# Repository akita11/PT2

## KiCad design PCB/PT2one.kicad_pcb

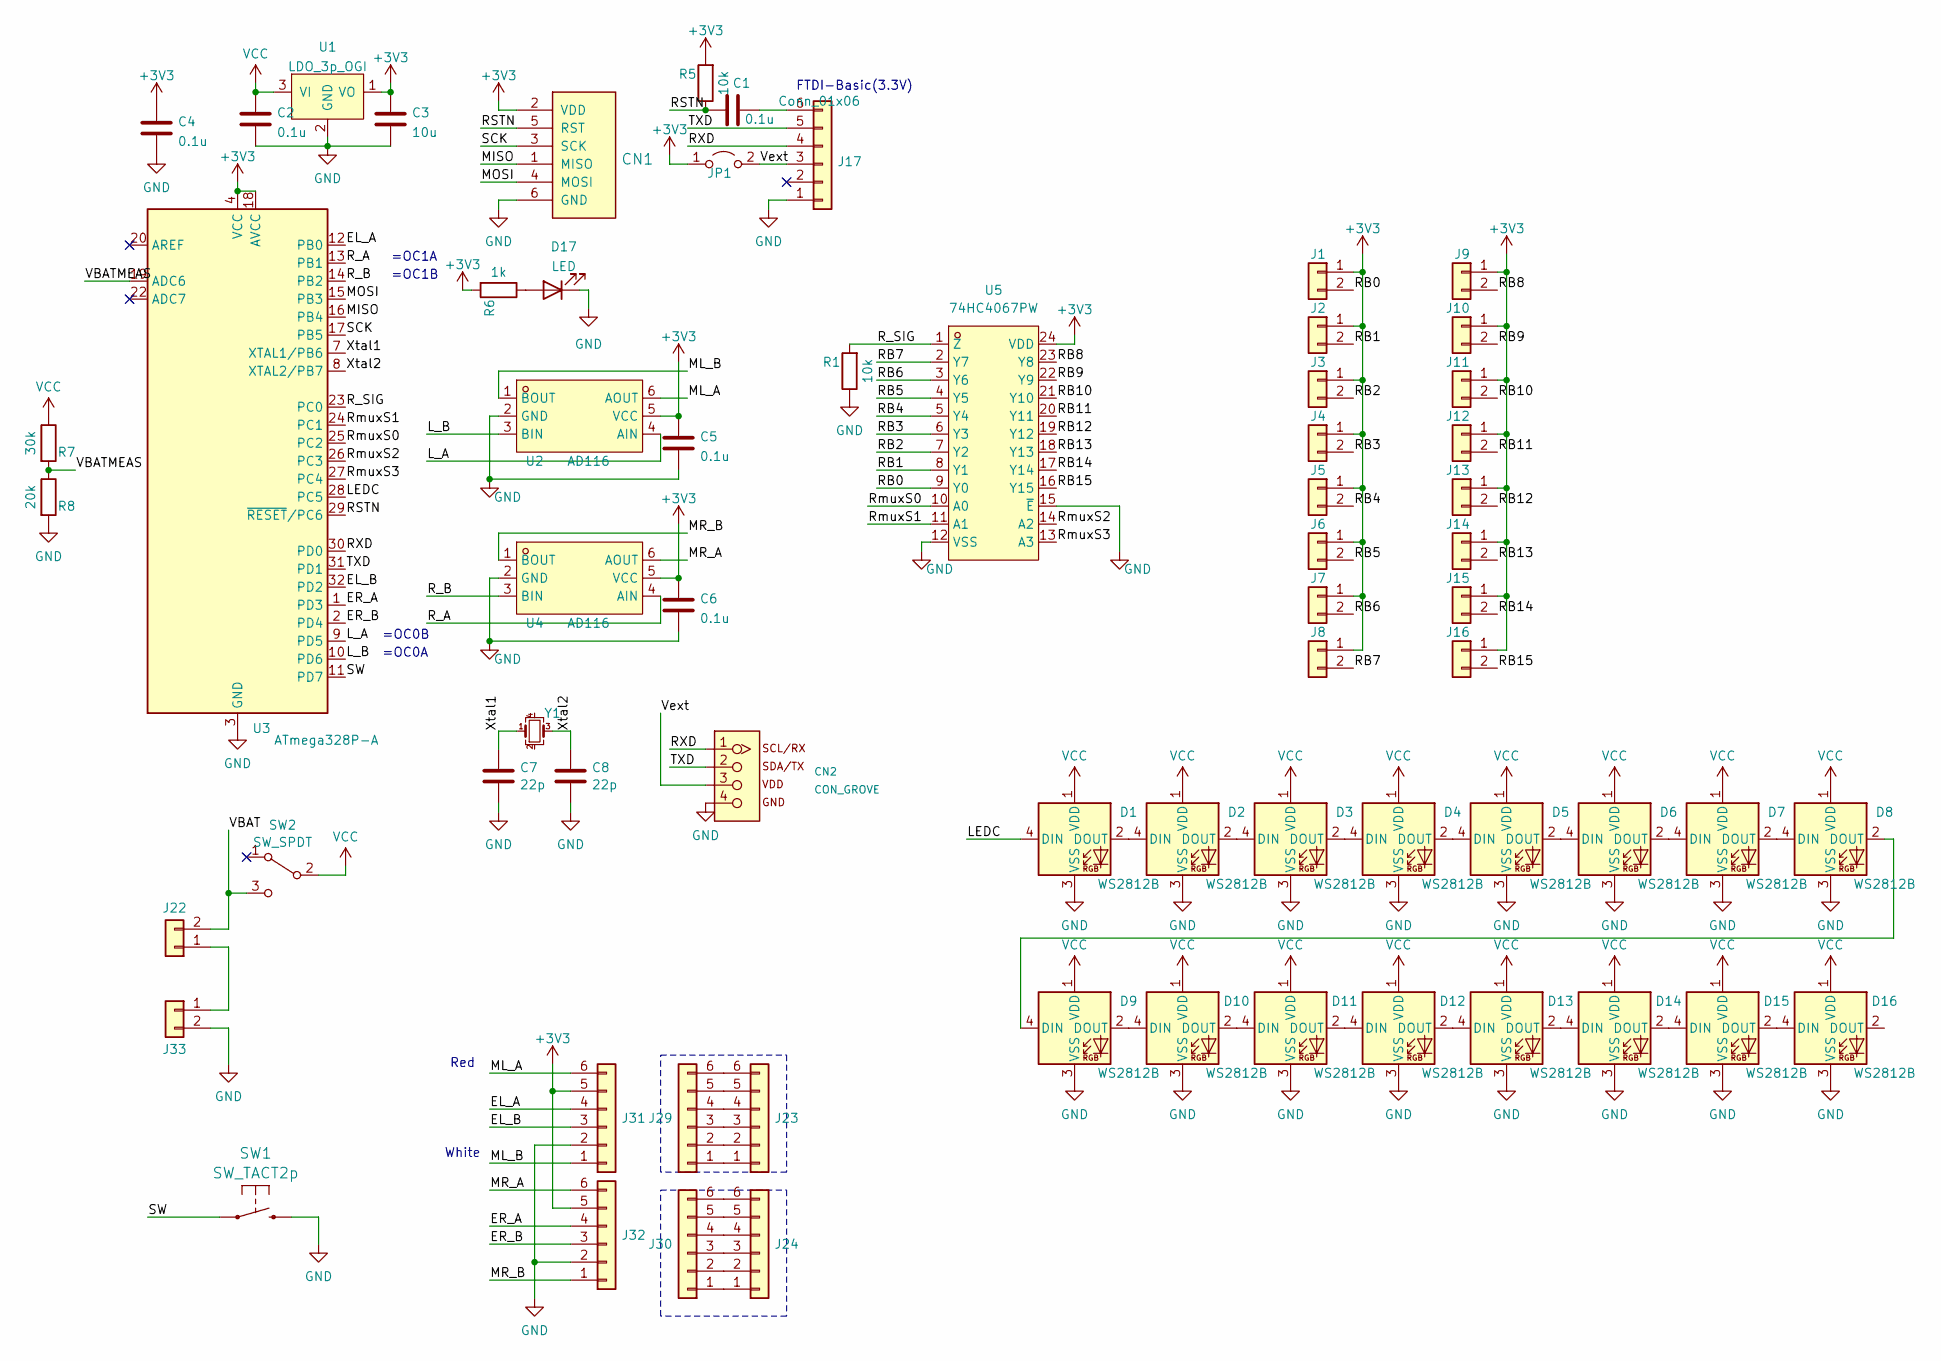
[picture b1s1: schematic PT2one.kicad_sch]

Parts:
C1, C2, C4, C5, C6: 0.1u; C_0603_1608Metric
C3: 10u; C_0603_1608Metric
C7, C8: 22p; C_0603_1608Metric
CN1: CON_AVRISP; PinHeader_2x03_P2.54mm_Vertical
CN2: CON_GROVE; CON_GROVE_H_roundPad
D1, D2, D3, D4, D5, D6, D7, D8, D9, D10, D11, D12, D13, D14, D15, D16: WS2812B; LED_WS2812B_PLCC4_5.0x5.0mm_P3.2mm
D17: LED; LED_0603_1608Metric
J1, J2, J3, J4, J5, J6, J7, J8, J9, J10, J11, J12, J13, J14, J15, J16: Conn_01x02; CON_MagConn2_NoTab
J17: Conn_01x06; PinSocket_1x06_P2.54mm_Horizontal
J22: Conn_01x02; BAT_UM3x1
J23, J24: Conn_01x06; CON_PinSocket_1.5mmx6V
J29, J30: Conn_01x06; PinHeader_2x03_P2.54mm_Vertical
J31, J32: Conn_01x06; PinHeader_2x03_P2.54mm_Horizontal
J33: Conn_01x02; BAT_UM3x2
JP1: Jumper_2_Open; SolderJumper-2_P1.3mm_Open_Pad1.0x1.5mm
R1, R5: 10k; R_0603_1608Metric
R6: 1k; R_0603_1608Metric
R7: 30k; R_0603_1608Metric
R8: 20k; R_0603_1608Metric
SW1: SW_TACT2p; SW_PUSH-12mm
SW2: SW_SPDT; SW_SK-12D11VG3
U1: LDO_3p_OGI; SOT-89-3; LCSC C920514
U2, U4: AD116; SOT-23-6_L2.9-W1.6-P0.95-LS2.8-BL; LCSC Part C7463412
U3: ATmega328P-A; TQFP-32_7x7mm_P0.8mm; LCSC C14877
U5: 74HC4067PW; TSSOP-24_L7.8-W4.4-P0.65-LS6.4-BL; MPN 74HC4067PW(LX); LCSC Part C22390251
Y1: Crystal_GND24_Small; Crystal_SMD_2520-4Pin_2.5x2.0mm

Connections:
+3V3: C3.1, C4.1, C5.1, C6.1, CN1.2 (VDD), J1.1, J2.1, J3.1, J4.1, J5.1, J6.1, J7.1, J8.1, J9.1, J10.1, J11.1, J12.1, J13.1, J14.1, J15.1, J16.1, J31.5, J32.5, JP1.1 (A), R5.2, R6.2, U1.1 (VO), U2.5 (VCC), U3.4 (VCC), U3.6 (VCC), U3.18 (AVCC), U4.5 (VCC), U5.24 (VDD)
/EL_A: J31.4, U3.12 (PB0)
/EL_B: J31.3, U3.32 (PD2)
/ER_A: J32.4, U3.1 (PD3)
/ER_B: J32.3, U3.2 (PD4)
/LEDC: D1.4 (DIN), U3.28 (PC5)
/L_A: U2.4 (AIN), U3.9 (PD5)
/L_B: U2.3 (BIN), U3.10 (PD6)
/MISO: CN1.1 (MISO), U3.16 (PB4)
/ML_A: J31.6, U2.6 (AOUT)
/ML_B: J31.1, U2.1 (BOUT)
/MOSI: CN1.4 (MOSI), U3.15 (PB3)
/MR_A: J32.6, U4.6 (AOUT)
/MR_B: J32.1, U4.1 (BOUT)
/RB0: J1.2, U5.9 (Y0)
/RB1: J2.2, U5.8 (Y1)
/RB2: J3.2, U5.7 (Y2)
/RB3: J4.2, U5.6 (Y3)
/RB4: J5.2, U5.5 (Y4)
/RB5: J6.2, U5.4 (Y5)
/RB6: J7.2, U5.3 (Y6)
/RB7: J8.2, U5.2 (Y7)
/RB8: J9.2, U5.23 (Y8)
/RB9: J10.2, U5.22 (Y9)
/RB10: J11.2, U5.21 (Y10)
/RB11: J12.2, U5.20 (Y11)
/RB12: J13.2, U5.19 (Y12)
/RB13: J14.2, U5.18 (Y13)
/RB14: J15.2, U5.17 (Y14)
/RB15: J16.2, U5.16 (Y15)
/RSTN: C1.1, CN1.5 (RST), R5.1, U3.29 (~RESET/PC6)
/RXD: CN2.1, J17.4, U3.30 (PD0)
/R_A: U3.13 (PB1), U4.4 (AIN)
/R_B: U3.14 (PB2), U4.3 (BIN)
/R_SIG: R1.2, U3.23 (PC0), U5.1 (Z)
/RmuxS0: U3.25 (PC2), U5.10 (A0)
/RmuxS1: U3.24 (PC1), U5.11 (A1)
/RmuxS2: U3.26 (PC3), U5.14 (A2)
/RmuxS3: U3.27 (PC4), U5.13 (A3)
/SCK: CN1.3 (SCK), U3.17 (PB5)
/SW: SW1.1, U3.11 (PD7)
/TXD: CN2.2, J17.5, U3.31 (PD1)
/VBAT: J22.2, SW2.3 (C)
/VBATMEAS: R7.2, R8.1, U3.19 (ADC6)
/Vext: CN2.3, J17.3, JP1.2 (B)
/Xtal1: C7.1, U3.7 (XTAL1/PB6), Y1.1
/Xtal2: C8.1, U3.8 (XTAL2/PB7), Y1.3
GND: C2.2, C3.2, C4.2, C5.2, C6.2, C7.2, C8.2, CN1.6 (GND), CN2.4, D1.3 (VSS), D2.3 (VSS), D3.3 (VSS), D4.3 (VSS), D5.3 (VSS), D6.3 (VSS), D7.3 (VSS), D8.3 (VSS), D9.3 (VSS), D10.3 (VSS), D11.3 (VSS), D12.3 (VSS), D13.3 (VSS), D14.3 (VSS), D15.3 (VSS), D16.3 (VSS), D17.1 (K), J17.1, J31.2, J32.2, J33.2, R1.1, R8.2, SW1.2, U1.2 (GND), U2.2 (GND), U3.3 (GND), U3.5 (GND), U3.21 (GND), U4.2 (GND), U5.12 (VSS), U5.15 (~E)
unnamed: D1.2 (DOUT), D2.4 (DIN)
unnamed: D2.2 (DOUT), D3.4 (DIN)
unnamed: D3.2 (DOUT), D4.4 (DIN)
unnamed: D4.2 (DOUT), D5.4 (DIN)
unnamed: D5.2 (DOUT), D6.4 (DIN)
unnamed: D6.2 (DOUT), D7.4 (DIN)
unnamed: D7.2 (DOUT), D8.4 (DIN)
unnamed: D8.2 (DOUT), D9.4 (DIN)
unnamed: D9.2 (DOUT), D10.4 (DIN)
unnamed: D10.2 (DOUT), D11.4 (DIN)
unnamed: D11.2 (DOUT), D12.4 (DIN)
unnamed: D12.2 (DOUT), D13.4 (DIN)
unnamed: D13.2 (DOUT), D14.4 (DIN)
unnamed: D14.2 (DOUT), D15.4 (DIN)
unnamed: D15.2 (DOUT), D16.4 (DIN)
unnamed: D17.2 (A), R6.1
unnamed: C1.2, J17.6
unnamed: J22.1, J33.1
unnamed: J23.1, J29.1
unnamed: J23.2, J29.2
unnamed: J23.3, J29.3
unnamed: J23.4, J29.4
unnamed: J23.5, J29.5
unnamed: J23.6, J29.6
unnamed: J24.1, J30.1
unnamed: J24.2, J30.2
unnamed: J24.3, J30.3
unnamed: J24.4, J30.4
unnamed: J24.5, J30.5
unnamed: J24.6, J30.6
VCC: C2.1, D1.1 (VDD), D2.1 (VDD), D3.1 (VDD), D4.1 (VDD), D5.1 (VDD), D6.1 (VDD), D7.1 (VDD), D8.1 (VDD), D9.1 (VDD), D10.1 (VDD), D11.1 (VDD), D12.1 (VDD), D13.1 (VDD), D14.1 (VDD), D15.1 (VDD), D16.1 (VDD), R7.1, SW2.2 (B), U1.3 (VI)

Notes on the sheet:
Red
FTDI-Basic(3.3V)
=OC1A
White
=OC1B
=OC0B
=OC0A

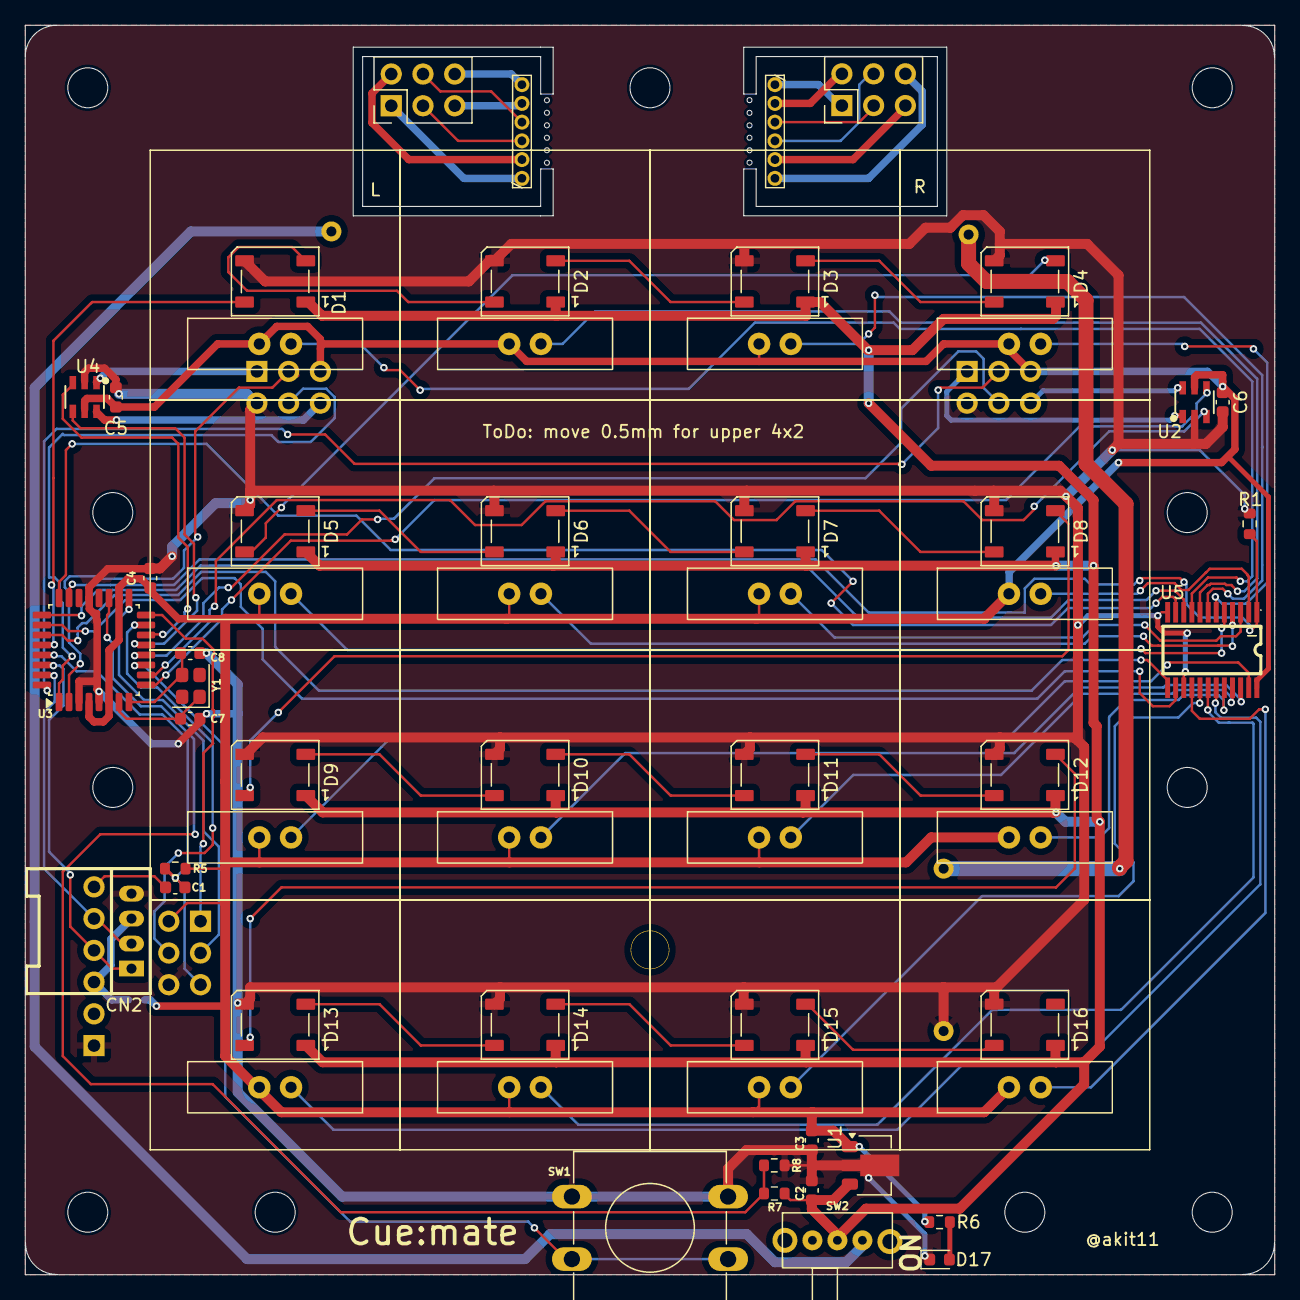
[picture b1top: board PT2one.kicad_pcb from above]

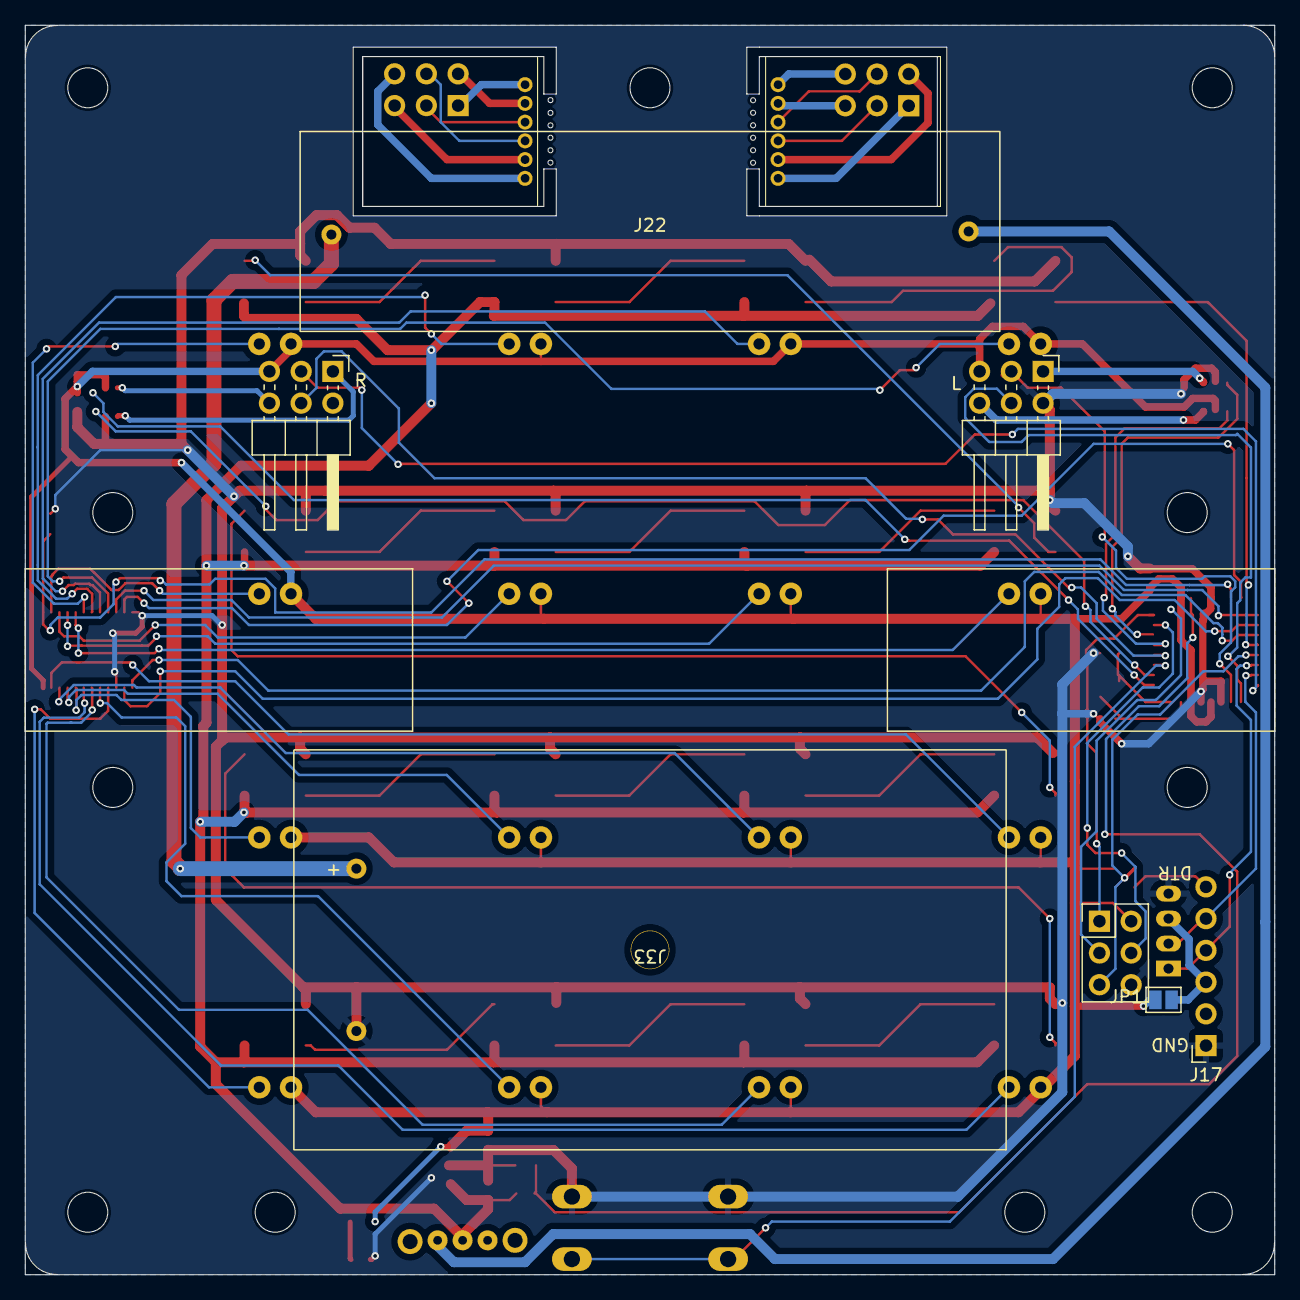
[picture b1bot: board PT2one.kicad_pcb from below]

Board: 2 copper layers, 100.0 x 100.0 mm, 66 parts (7 on the bottom side), 79 nets.

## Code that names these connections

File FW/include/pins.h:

#pragma once
// PT2.kicad_sch (U3 = ATmega328P-A) のネット名にあわせたピン定義。
// Arduinoピン番号は標準の bare-328P マッピング
// (D0-D7=PD0-7, D8-D13=PB0-5, A0-A5=PC0-5) に基づく。

#include <Arduino.h>

// ---- 抵抗マトリクス (16ch、CD74HC4067等の16:1アナログマルチプレクサ経由) ----
// 全16箇所のセル抵抗の駆動側は3.3Vに直結(GPIO不要)。
// センス側16本をマルチプレクサでSIG 1本に集約し、SIG-GND間に共通の
// プルダウン抵抗(R_PD, 10kΩ)を1本だけ実装する。
// マルチプレクサのINHはGND直結で常時イネーブルとする想定。
// ISPヘッダ(MOSI/MISO/SCK, D11-D13)とは衝突しないようA1-A3に割当。
constexpr uint8_t PIN_RM_MUX_S0 = A2;  // PC2        - マルチプレクサ アドレスbit0
constexpr uint8_t PIN_RM_MUX_S1 = A1;  // PC1        - マルチプレクサ アドレスbit1
constexpr uint8_t PIN_RM_MUX_S2 = A3;  // PC3        - マルチプレクサ アドレスbit2
constexpr uint8_t PIN_RM_MUX_S3 = A4;  // PC4        - マルチプレクサ アドレスbit3
constexpr uint8_t PIN_RM_MUX_SIG = A0; // PC0 / ADC0 - マルチプレクサ共通出力(ADC入力)

// ---- モータ (AD116ドライバ、AIN/BIN = PWM/方向の2線インターフェース) ----
constexpr uint8_t PIN_R_A = 5;  // PD5 / OC0B - 左モータ AIN
constexpr uint8_t PIN_R_B = 6;  // PD6 / OC0A - 左モータ BIN
constexpr uint8_t PIN_L_A = 9;  // PB1 / OC1A - 右モータ AIN
constexpr uint8_t PIN_L_B = 10; // PB2 / OC1B - 右モータ BIN

// ---- ロータリエンコーダ (2相、PCINTで計測) ----
constexpr uint8_t PIN_ER_A = 8; // PB0 / PCINT0  - 左エンコーダA
constexpr uint8_t PIN_ER_B = 2; // PD2 / PCINT18 - 左エンコーダB
constexpr uint8_t PIN_EL_A = 3; // PD3 / PCINT19 - 右エンコーダA
constexpr uint8_t PIN_EL_B = 4; // PD4 / PCINT20 - 右エンコーダB

// ---- LED (WS2812 x16, 単線シリアルチェーン) ----
constexpr uint8_t PIN_LEDC = A5; // PC5
constexpr uint8_t LED_COUNT = 16;

// ---- その他 ----
constexpr uint8_t PIN_SW = 7;  // PD7 - スタートスイッチ
